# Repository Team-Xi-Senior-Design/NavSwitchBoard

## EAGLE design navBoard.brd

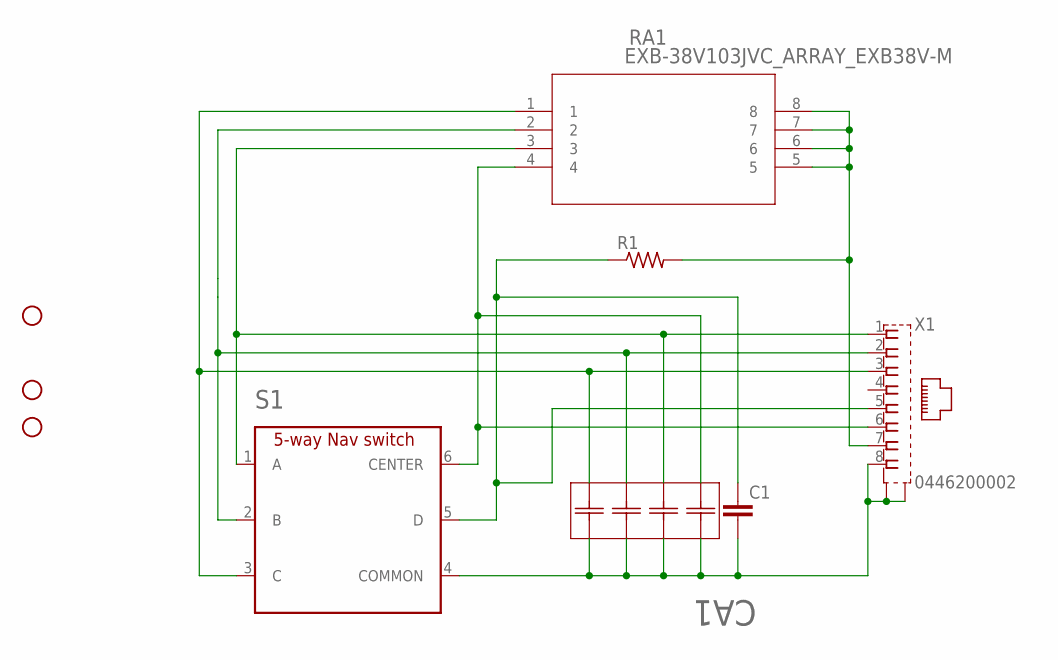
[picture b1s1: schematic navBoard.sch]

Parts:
C1: C-EUC0603K; C0603K
CA1: CKCL44X5R0J104M085AACKCL44-M; CKCL44-M
H1, H2, H4: STAND-OFF
R1: R-US_R0603; R0603
RA1: EXB-38V103JVC_ARRAY_EXB38V-M; C_ARRAY_EXB38V-M
S1: SKQUCAA010
X1: 0446200002

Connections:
COMMON: C1.2, CA1.5 (52), CA1.6 (64), CA1.7 (76), CA1.8 (88), S1.4 (COMMON), X1.8, X1.S@1 (S1), X1.S@2 (S2)
unnamed: CA1.2 (25), RA1.3, S1.1 (A), X1.1
unnamed: CA1.3 (33), RA1.2, S1.2 (B), X1.2
unnamed: CA1.4 (41), RA1.1, S1.3 (C), X1.3
unnamed: CA1.1 (17), RA1.4, S1.6 (CENTER), X1.6
unnamed: C1.1, R1.1, S1.5 (D), X1.5
unnamed: R1.2, RA1.5, RA1.6, RA1.7, RA1.8, X1.7

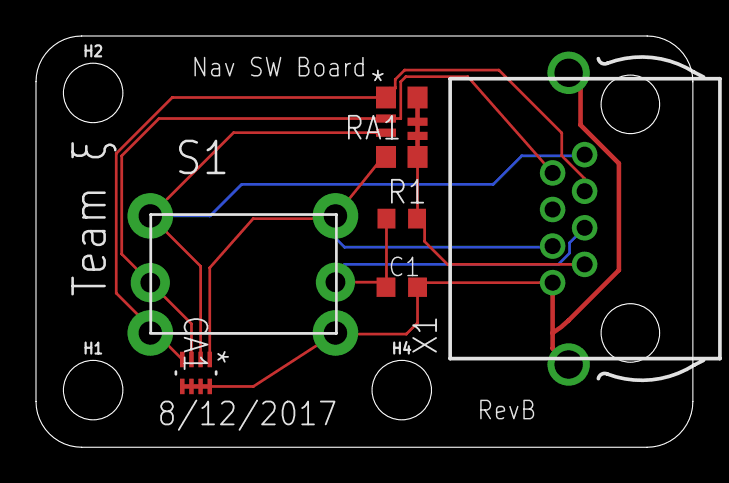
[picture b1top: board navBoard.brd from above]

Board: 2 copper layers, 36.5 x 22.8 mm, 9 parts (0 on the bottom side), 7 nets.

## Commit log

2017-12-08 RevB
    Ordered!

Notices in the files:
parts and their libraries:
SparkFun-Hardware: Licensing: Creative Commons ShareAlike 4.0 International - https://creativecommons.org/licenses/by-sa/4.0
